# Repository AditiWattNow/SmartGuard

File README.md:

# SmartGuard — AI-Powered Railway Platform Crowd Safety System

> **Hackathon Project** | Hardware + Software | Indian Railways Safety Track

## The Problem

On **February 15, 2025**, a crowd crush at New Delhi Railway Station killed **18 people** and injured 15 others — triggered by train delays creating dangerous platform overcrowding. Indian Railways subsequently identified **60 high-traffic stations** requiring immediate crowd management upgrades.

Existing solutions react *after* dangerous density is reached. SmartGuard **predicts** breaches before they happen.

---

## What SmartGuard Does

| Layer | What it is |
|-------|-----------|
| **Hardware** | Custom PCB sensor node (ESP32-S3 + PIR + ToF + LoRa) per zone |
| **Backend** | FastAPI server with time-series crowd data + anomaly detection |
| **Dashboard** | Live SVG station map + real-time alerts + trend prediction |
| **AI Model** | Linear regression slope on 5-reading window → estimated minutes to breach |

**Key differentiator:** SmartGuard gives station operators an **8–15 minute warning** before a dangerous threshold is reached — time to open alternate gates, redirect crowds, or delay train boarding. Real-time monitoring only tells you what's *already* happening.

---

## Architecture

```
[ESP32-S3 Node] ──WiFi/LoRa──▶ [FastAPI Backend] ──REST──▶ [Dashboard]
    ↑                                   ↓
PIR + VL53L1X                    SQLite DB
sensors                          Prediction Engine
                                 Alert Generator
```

**Kavach 4.0 compatible:** SmartGuard data format is designed for integration with Indian Railways' existing Kavach ATP system API. Kavach prevents train collisions — SmartGuard prevents platform crush. They are complementary, not competing.

---

## Repository Structure

```
smartguard/
├── backend/
│   ├── main.py              # FastAPI server — all 4 endpoints
│   └── requirements.txt
├── firmware/
│   └── smartguard_node.ino  # ESP32-S3 Arduino sketch
├── frontend/
│   └── index.html           # Complete single-file dashboard
├── hardware/                # KiCad PCB project (your partner's domain)
│   ├── smartguard_node.kicad_sch
│   ├── smartguard_node.kicad_pcb
│   └── gerbers/
└── docs/
    ├── architecture.png
    └── deployment-spec.md
```

---

## Running Locally

### Backend

```bash
cd backend
pip install -r requirements.txt
uvicorn main:app --reload --host 0.0.0.0 --port 8000
```

The server starts with:
- **Seeded historical data** (2 hours of realistic crowd patterns)
- **Mock sensor simulator** running in background — no hardware needed for demo
- **SQLite database** (`smartguard.db`) auto-created on first run

### Frontend

Just open `frontend/index.html` in a browser. No build step needed.

> If you get CORS errors, make sure the backend is running on `localhost:8000` (default).  
> For deployment, update `const API = "..."` in `index.html` to your server URL.

---

## API Endpoints

| Method | Endpoint | Description |
|--------|----------|-------------|
| `POST` | `/sensor` | Receive data from ESP32 nodes |
| `GET`  | `/zones` | Live crowd state for all zones |
| `GET`  | `/history/{zone_id}?minutes=60` | Time-series data for chart |
| `GET`  | `/alerts?limit=20` | Recent alert feed |
| `GET`  | `/stats/summary` | Header KPI cards |

### Example sensor POST (from ESP32 or test):
```bash
curl -X POST http://localhost:8000/sensor \
  -H "Content-Type: application/json" \
  -d '{"zone_id": "P1", "count": 145}'
```

---

## Zone Configuration

Zones are defined in `backend/main.py`:

```python
ZONES = {
    "P1": {"name": "Platform 1 - Gate A", "capacity": 200, ...},
    "P2": {"name": "Platform 2 - Gate B", "capacity": 180, ...},
    "C1": {"name": "Central Concourse",   "capacity": 400, ...},
    ...
}

THRESHOLDS = {"safe": 0.60, "warning": 0.80}  # fraction of capacity
```

Modify these to match any real station's layout.

---

## Prediction Model

SmartGuard uses a **least-squares linear regression** on the 10 most recent readings per zone:

1. Compute slope (people/second) from the time-series
2. If slope is positive, estimate seconds until 80% capacity threshold
3. Convert to minutes and surface in the UI as "Breach in ~N min"

This is equivalent to `sklearn.linear_model.LinearRegression` on a rolling window. For production, this can be upgraded to `IsolationForest` for anomaly detection or an LSTM for multi-step forecasting.

---

## Hardware BOM (per node) — ~₹2,500

| Component | Part | ~Cost |
|-----------|------|-------|
| MCU | ESP32-S3 DevKitC | ₹800 |
| Motion sensor × 2 | HC-SR501 PIR | ₹80 |
| Distance sensor | VL53L1X ToF | ₹350 |
| Radio | SX1276 LoRa module | ₹450 |
| Battery management | TP4056 IC | ₹40 |
| PCB fabrication (JLCPCB) | 4-layer, 5 units | ₹600 |
| Misc (caps, LEDs, headers) | — | ₹180 |

**60 stations × avg 8 nodes = 480 nodes × ₹2,500 = ₹12 lakh total hardware cost.**
This is the cost of one Kavach installation on a 1km track segment.

---

## Deployment Path

1. **Phase 1 — Pilot** (3 months): Install at 2 platforms of New Delhi station. Validate prediction accuracy against manual crowd counts.
2. **Phase 2 — Refinement** (3 months): Tune thresholds, integrate train delay API for better surge prediction.
3. **Phase 3 — Rollout** (6 months): Deploy to 60 identified high-risk stations. Integrate alerts into station master control room.

---

## Team

| Role | Responsibility |
|------|---------------|
| Hardware Engineer | PCB design (KiCad), ESP32 firmware, sensor integration |
| Software Engineer | FastAPI backend, React dashboard, deployment |

---

## License

MIT License — open for Indian Railways adoption and modification.

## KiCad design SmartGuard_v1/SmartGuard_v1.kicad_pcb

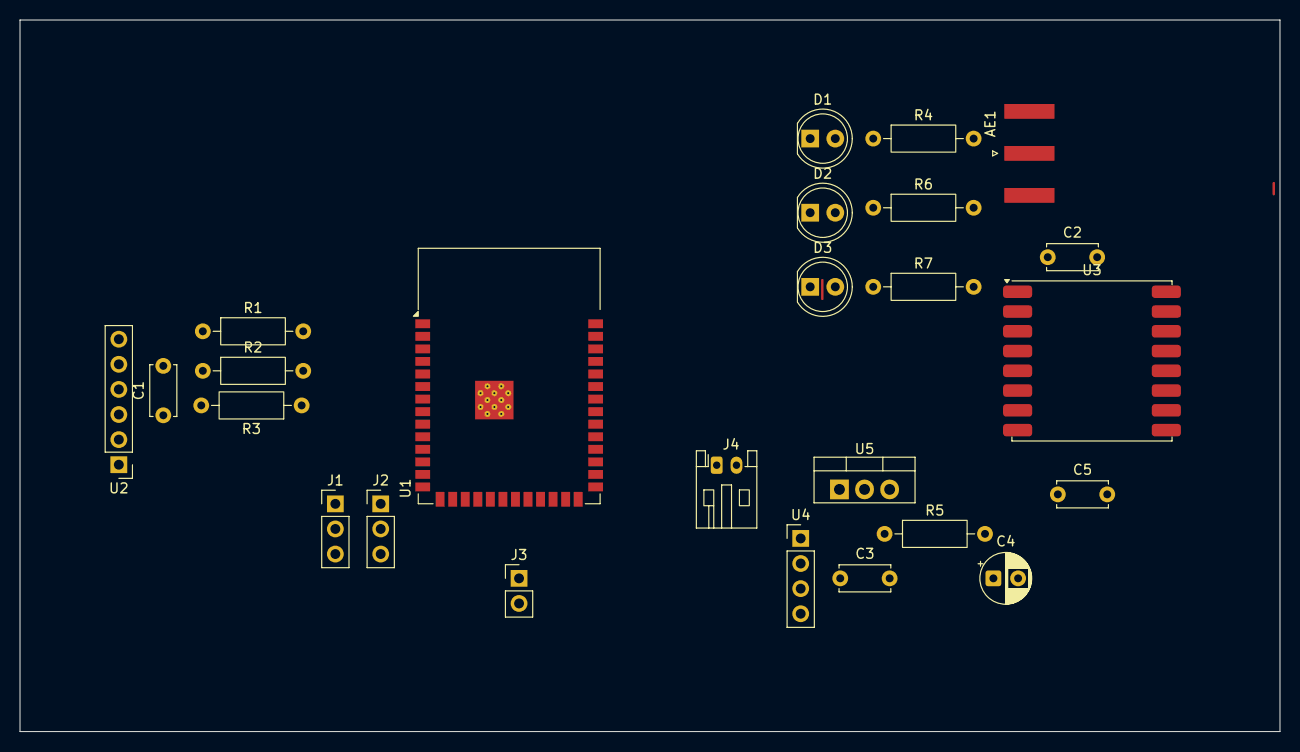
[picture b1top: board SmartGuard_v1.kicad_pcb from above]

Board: 2 copper layers, 127.5 x 72.0 mm, 25 parts (0 on the bottom side), 25 nets.

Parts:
AE1: Antenna; SMA_Amphenol_132289_EdgeMount
C1, C2, C3, C5: 100nF; C_Disc_D5.0mm_W2.5mm_P5.00mm
C4: 10uF; CP_Radial_D5.0mm_P2.50mm
D1, D2, D3: LED; LED_D5.0mm
J1, J2: Conn_01x03_Pin; PinHeader_1x03_P2.54mm_Vertical
J3: USB_C_Receptacle_USB2.0_16P; PinHeader_1x02_P2.54mm_Vertical
J4: Conn_01x02; JST_PH_S2B-PH-K_1x02_P2.00mm_Horizontal
R1: 10k; R_Axial_DIN0207_L6.3mm_D2.5mm_P10.16mm_Horizontal
R2, R3: 4.7k; R_Axial_DIN0207_L6.3mm_D2.5mm_P10.16mm_Horizontal
R4, R6, R7: 100R; R_Axial_DIN0207_L6.3mm_D2.5mm_P10.16mm_Horizontal
R5: 1.2k; R_Axial_DIN0207_L6.3mm_D2.5mm_P10.16mm_Horizontal
U1: ESP32-S3-WROOM-1
U2: VL53L1CXV0FY1; PinHeader_1x06_P2.54mm_Vertical
U3: RFM95W-868S2; HOPERF_RFM9XW_SMD
U4: TP4056-42-ESOP8; PinHeader_1x04_P2.54mm_Vertical
U5: AMS1117-3.3; TO-220-3_Vertical

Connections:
+3V3: C1.2, C5.1, R1.2, R2.1, R3.1, U1.2 (3V3), U3.13 (3.3V), U5.2 (VO)
+5V: J1.1 (VCC), J2.1 (VCC)
/I2C_SCL: R3.2, U1.5 (IO5)
/I2C_SDA: R2.2, U1.4 (IO4)
/LED_AMB: R7.1, U1.35 (IO42)
/LED_GRN: R6.1, U1.24 (IO47)
/LED_RED: R4.1, U1.16 (IO46)
/LORA_DIO0: U1.17 (IO9), U3.14 (DIO0)
/LORA_NSS: U1.23 (IO21), U3.5 (NSS)
/LORA_RST: U1.34 (IO41), U3.6 (RESET)
/PIR_A: J1.2 (PIR_A), U1.6 (IO6)
/PIR_B: J2.2 (PIR_B), U1.7 (IO7)
/SPI_MISO: U1.28 (IO35), U3.2 (MISO)
/SPI_MOSI: U1.11 (IO18), U3.3 (MOSI)
/SPI_SCK: U1.31 (IO38), U3.4 (SCK)
/TOF_XSHUT: U1.12 (IO8), U2.5 (XSHUT)
GND: C1.1, C2.2, C3.2, C4.2, C5.2, D1.1 (K), D2.1 (K), D3.1 (K), J1.3 (GND), J2.3 (GND), J4.2, R5.1, U1.1 (GND), U1.40 (GND), U1.41 (GND), U2.3 (GND), U2.4 (GND), U2.6 (GND), U3.10 (GND), U4.3 (GND)
unnamed: AE1.1 (A), U3.9 (ANT)
unnamed: D1.2 (A), R4.2
unnamed: D2.2 (A), R7.2
unnamed: D3.2 (A), R6.2
unnamed: C3.1, C4.1, J4.1 (VBAT), U5.3 (VI)
unnamed: R1.1, U1.3 (EN)
unnamed: R5.2, U4.2 (PROG)
VCC: C2.1, U4.4 (V_{CC})

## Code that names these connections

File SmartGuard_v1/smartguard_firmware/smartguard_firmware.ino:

// ============================================
// SmartGuard v1 — Firmware
// ESP32-S3-WROOM-1
// Far Away Hackathon 2026
// Theme: Railways
// ============================================

#include <Wire.h>
#include <VL53L1X.h>
#include <SPI.h>
#include <LoRa.h>
#include <ArduinoJson.h>

// ============================================
// PIN DEFINITIONS
// ============================================

// I2C - VL53L1X
#define I2C_SDA       4
#define I2C_SCL       5
#define TOF_XSHUT     8

// SPI - RFM95W LoRa
#define LORA_MOSI     18
#define LORA_MISO     35
#define LORA_SCK      38
#define LORA_NSS      21
#define LORA_RST      41
#define LORA_DIO0     9

// PIR Sensors
#define PIR_A         6
#define PIR_B         7

// Status LEDs
#define LED_RED       46
#define LED_AMB       42
#define LED_GRN       47

// ============================================
// CONFIGURATION
// ============================================

#define LORA_FREQ         868E6    // 868 MHz India ISM band
#define NODE_ID           "PF_01"  // Platform node ID - change per node
#define SEND_INTERVAL     30000    // Send data every 30 seconds
#define DENSITY_THRESHOLD_AMBER  10  // People count for amber alert
#define DENSITY_THRESHOLD_RED    20  // People count for red alert

// VL53L1X distance thresholds (mm)
// Anything closer than this = person detected in doorway
#define PERSON_DISTANCE   1200     // 1.2 metres

// ============================================
// GLOBAL VARIABLES
// ============================================

VL53L1X tofSensor;

int peopleCount     = 0;    // Running total of people on platform
int peopleIn        = 0;    // People entered this interval
int peopleOut       = 0;    // People exited this interval
bool lastBeamState  = false;// Last state of ToF beam
bool pirAState      = false;
bool pirBState      = false;
unsigned long lastSendTime  = 0;
unsigned long lastTofRead   = 0;
String alertLevel   = "GREEN";

// ============================================
// SETUP
// ============================================

void setup() {
  Serial.begin(115200);
  Serial.println("SmartGuard v1 — Booting...");

  // LED pins
  pinMode(LED_RED, OUTPUT);
  pinMode(LED_AMB, OUTPUT);
  pinMode(LED_GRN, OUTPUT);

  // PIR pins
  pinMode(PIR_A, INPUT);
  pinMode(PIR_B, INPUT);

  // Boot indicator — flash all LEDs
  flashAllLEDs(3);

  // Initialise I2C
  Wire.begin(I2C_SDA, I2C_SCL);
  Serial.println("I2C initialised");

  // Initialise VL53L1X
  pinMode(TOF_XSHUT, OUTPUT);
  digitalWrite(TOF_XSHUT, LOW);
  delay(10);
  digitalWrite(TOF_XSHUT, HIGH);
  delay(10);

  tofSensor.setTimeout(500);
  if (!tofSensor.init()) {
    Serial.println("ERROR: VL53L1X not found!");
    errorBlink(LED_RED);  // Fast red blink = sensor error
  } else {
    Serial.println("VL53L1X initialised");
    tofSensor.setDistanceMode(VL53L1X::Long);
    tofSensor.setMeasurementTimingBudget(50000);
    tofSensor.startContinuous(50);
  }

  // Initialise LoRa
  SPI.begin(LORA_SCK, LORA_MISO, LORA_MOSI, LORA_NSS);
  LoRa.setPins(LORA_NSS, LORA_RST, LORA_DIO0);

  if (!LoRa.begin(LORA_FREQ)) {
    Serial.println("ERROR: LoRa not found!");
    errorBlink(LED_AMB);  // Fast amber blink = LoRa error
  } else {
    Serial.println("LoRa initialised at 868 MHz");
    LoRa.setSpreadingFactor(9);       // SF9 - good range/speed balance
    LoRa.setSignalBandwidth(125E3);   // 125 kHz bandwidth
    LoRa.setCodingRate4(5);           // 4/5 coding rate
    LoRa.setTxPower(17);              // 17 dBm transmit power
  }

  // Ready — show green
  setLED("GREEN");
  Serial.println("SmartGuard ready!");
  Serial.print("Node ID: ");
  Serial.println(NODE_ID);
}

// ============================================
// MAIN LOOP
// ============================================

void loop() {
  unsigned long now = millis();

  // Read ToF sensor every 100ms
  if (now - lastTofRead >= 100) {
    readToFSensor();
    lastTofRead = now;
  }

  // Read PIR sensors
  pirAState = digitalRead(PIR_A);
  pirBState = digitalRead(PIR_B);

  // Calculate density and update LEDs
  updateAlertLevel();

  // Send LoRa packet every 30 seconds
  if (now - lastSendTime >= SEND_INTERVAL) {
    sendLoRaPacket();
    lastSendTime = now;
  }
}

// ============================================
// TOF SENSOR — PEOPLE COUNTING
// ============================================

void readToFSensor() {
  if (!tofSensor.dataReady()) return;

  int distance = tofSensor.read();

  // Person detected if closer than threshold
  bool beamBroken = (distance < PERSON_DISTANCE);

  // Rising edge — person just walked into beam
  if (beamBroken && !lastBeamState) {
    // Simple direction detection using PIR
    // If PIR_A triggered recently = entering platform
    // If PIR_B triggered recently = exiting platform
    if (pirAState) {
      peopleCount++;
      peopleIn++;
      Serial.print("Person IN — Total: ");
      Serial.println(peopleCount);
    } else if (pirBState) {
      if (peopleCount > 0) peopleCount--;
      peopleOut++;
      Serial.print("Person OUT — Total: ");
      Serial.println(peopleCount);
    } else {
      // Default — assume entering
      peopleCount++;
      peopleIn++;
      Serial.print("Person detected — Total: ");
      Serial.println(peopleCount);
    }
  }

  lastBeamState = beamBroken;
}

// ============================================
// ALERT LEVEL + LED CONTROL
// ============================================

void updateAlertLevel() {
  if (peopleCount >= DENSITY_THRESHOLD_RED) {
    alertLevel = "RED";
    setLED("RED");
  } else if (peopleCount >= DENSITY_THRESHOLD_AMBER) {
    alertLevel = "AMBER";
    setLED("AMBER");
  } else {
    alertLevel = "GREEN";
    setLED("GREEN");
  }
}

void setLED(String level) {
  // Turn all off first
  digitalWrite(LED_RED, LOW);
  digitalWrite(LED_AMB, LOW);
  digitalWrite(LED_GRN, LOW);

  if (level == "RED")   digitalWrite(LED_RED, HIGH);
  if (level == "AMBER") digitalWrite(LED_AMB, HIGH);
  if (level == "GREEN") digitalWrite(LED_GRN, HIGH);
}

// ============================================
// LORA TRANSMISSION
// ============================================

void sendLoRaPacket() {
  // Build JSON payload
  StaticJsonDocument<256> doc;
  doc["node"]    = NODE_ID;
  doc["count"]   = peopleCount;
  doc["in"]      = peopleIn;
  doc["out"]     = peopleOut;
  doc["alert"]   = alertLevel;
  doc["pir_a"]   = pirAState;
  doc["pir_b"]   = pirBState;
  doc["uptime"]  = millis() / 1000;

  String payload;
  serializeJson(doc, payload);

  // Send via LoRa
  LoRa.beginPacket();
  LoRa.print(payload);
  LoRa.endPacket();

  Serial.print("LoRa sent: ");
  Serial.println(payload);

  // Reset interval counters
  peopleIn  = 0;
  peopleOut = 0;
}

// ============================================
// UTILITY FUNCTIONS
// ============================================

void flashAllLEDs(int times) {
  for (int i = 0; i < times; i++) {
    digitalWrite(LED_RED, HIGH);
    digitalWrite(LED_AMB, HIGH);
    digitalWrite(LED_GRN, HIGH);
    delay(200);
    digitalWrite(LED_RED, LOW);
    digitalWrite(LED_AMB, LOW);
    digitalWrite(LED_GRN, LOW);
    delay(200);
  }
}

void errorBlink(int pin) {
  // Fast blink forever to indicate error
  Serial.println("HALTED — Check sensor connection");
  while (true) {
    digitalWrite(pin, HIGH);
    delay(100);
    digitalWrite(pin, LOW);
    delay(100);
  }
}

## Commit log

2026-06-11 Add PCB design files and firmware
2026-06-11 Revise README for SmartGuard project details
    Expanded the README to provide detailed information about the SmartGuard system, including the problem it addresses, solution, system architecture, hardware specifications, firmware requirements, sof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
2026-06-11 Add hardware files
2026-06-12 Add PCB screenshots
2026-06-12 Add PCB preview images to README
2026-06-12 add sch, pcb, 3-D view
2026-06-13 Add backend, frontend and firmware - software stack
2026-06-13 Add KiCad hardware files to main
